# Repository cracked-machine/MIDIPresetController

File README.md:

# MIDIPresetController

This is a simple MIDI controller for Guitar FX pedals. An [STM32L011D4](HW/techdocs/stm32l011d4_datasheet.pdf) is used to detect stomp switch presses by the user and output MIDI signals via a DIN5 connector.

The project is designed to fit into a [Hammond 1455J1602](HW/techdocs/Hammond_1455J1602BK_enclosure.pdf) enclosure. 

3D models can be found here for the [end plate bezel](https://3dviewer.net#model=https://raw.githubusercontent.com/cracked-machine/MIDIPresetController/master/HW/res/3d/1455J1602/J%20Bezel%20Closed.igs) and [main extrusion](https://3dviewer.net#model=https://raw.githubusercontent.com/cracked-machine/MIDIPresetController/master/HW/res/3d/1455J1602/J%20Extrusion%20160mm.igs)

This is an extruded alu case. The PCB slides in from one side.  

The stomp switches are panel mounted on the front side of the enclosure with connecting wires to rear of the PCB (via molex KK254 connectors)

It is powered by a 3v3 CR2032 cell, held by a battery clip, which is mounted on the rear side of the PCB. Internal voltage reference of the MCU is used to measure remaining battery. An LED mounted on the front of the PCB and connected to GPIO indicates low battery power to the user.

The MIDI channel can be selected using the DIP switch on the rear side of the PCB.  The MIDI output connector (DIN5) is mounted to the end plate bezel of the enclosure

A 10-pin ARM SWD programming connector is mounted to the rear of the PCB. 

A removable "belly plate" on the enclosure provides access to the battery, MIDI DIP switch and SWD connector.  

### Development Environment

YOu can run this project from within a container and program the board via a Segger JLink. This uses `JLinkRemoteServer` to establish a connect between the container environment and the device connected to the `host` PC. To enable this connection, run the follow command on the __host__ terminal:

```
JLinkRemoteServer --select USB
```

See [stm32_dev_docker/README.md](https://github.com/cracked-machine/stm32_dev_docker) for instructions on using the `development environment` for this project.

Note: this project is currently configured for a specific version of CMake and ARM compiler. The paths are hard-coded in the project [here](.vscode/settings.json)

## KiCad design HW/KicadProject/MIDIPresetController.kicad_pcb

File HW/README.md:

# MIDIPresetController

This is the doc for the [hardware project files](KicadProject)

This project has the following dependencies to [KicadLibrary](HW/KicadLibrary):

- BATTERY/GenericCoinCellHolders/GenericCoinCellHolders

## Schematic 

1. System

2. Input 

3. MCU

4. Output

## Pinout 

## PCB

1. Front

2. Back

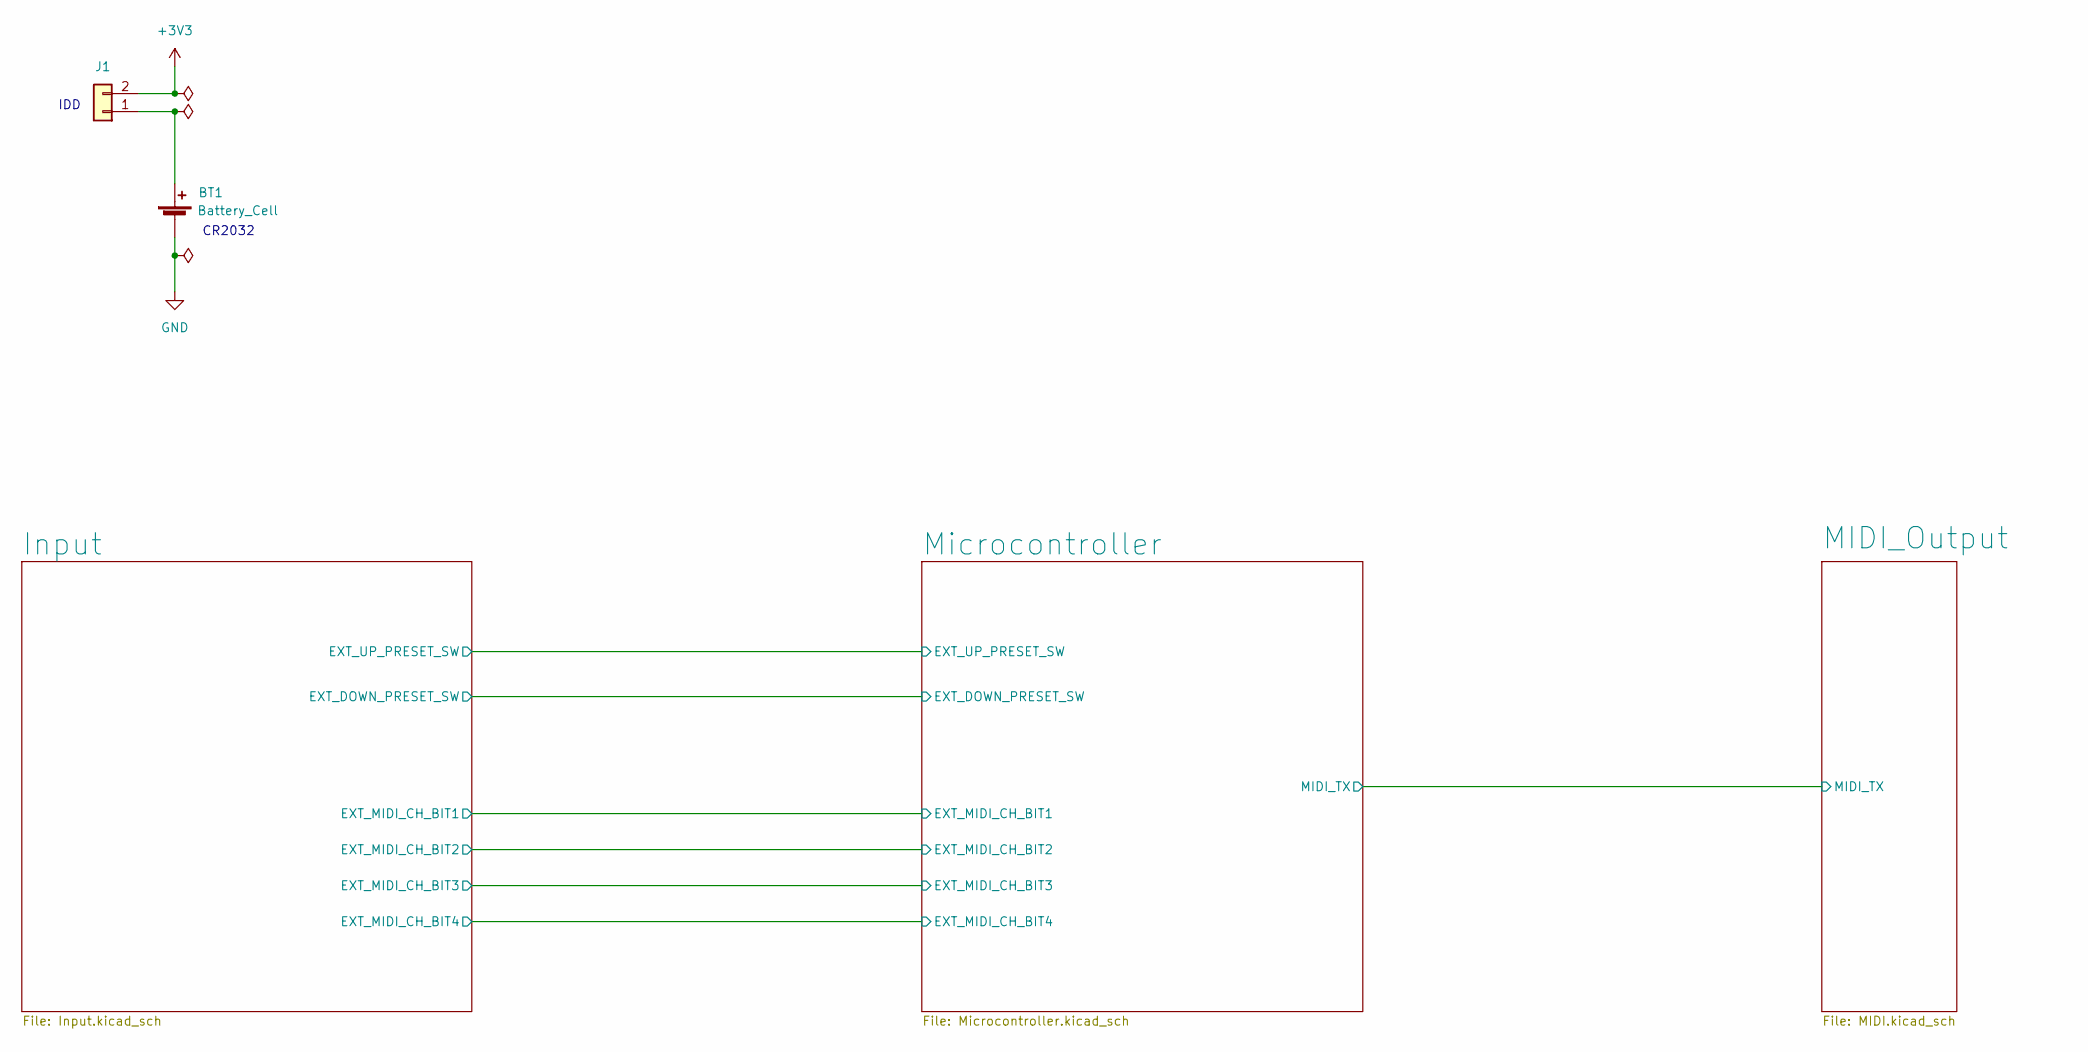
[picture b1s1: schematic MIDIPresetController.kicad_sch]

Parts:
BT1: Battery_Cell; CR2032
J1: Conn_01x02; PinHeader_1x02_P2.54mm_Vertical

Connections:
+3V3: J1.2; also elsewhere on the board
GND: BT1.2 (-); also elsewhere on the board
unnamed: BT1.1 (+), J1.1

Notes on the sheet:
CR2032
IDD

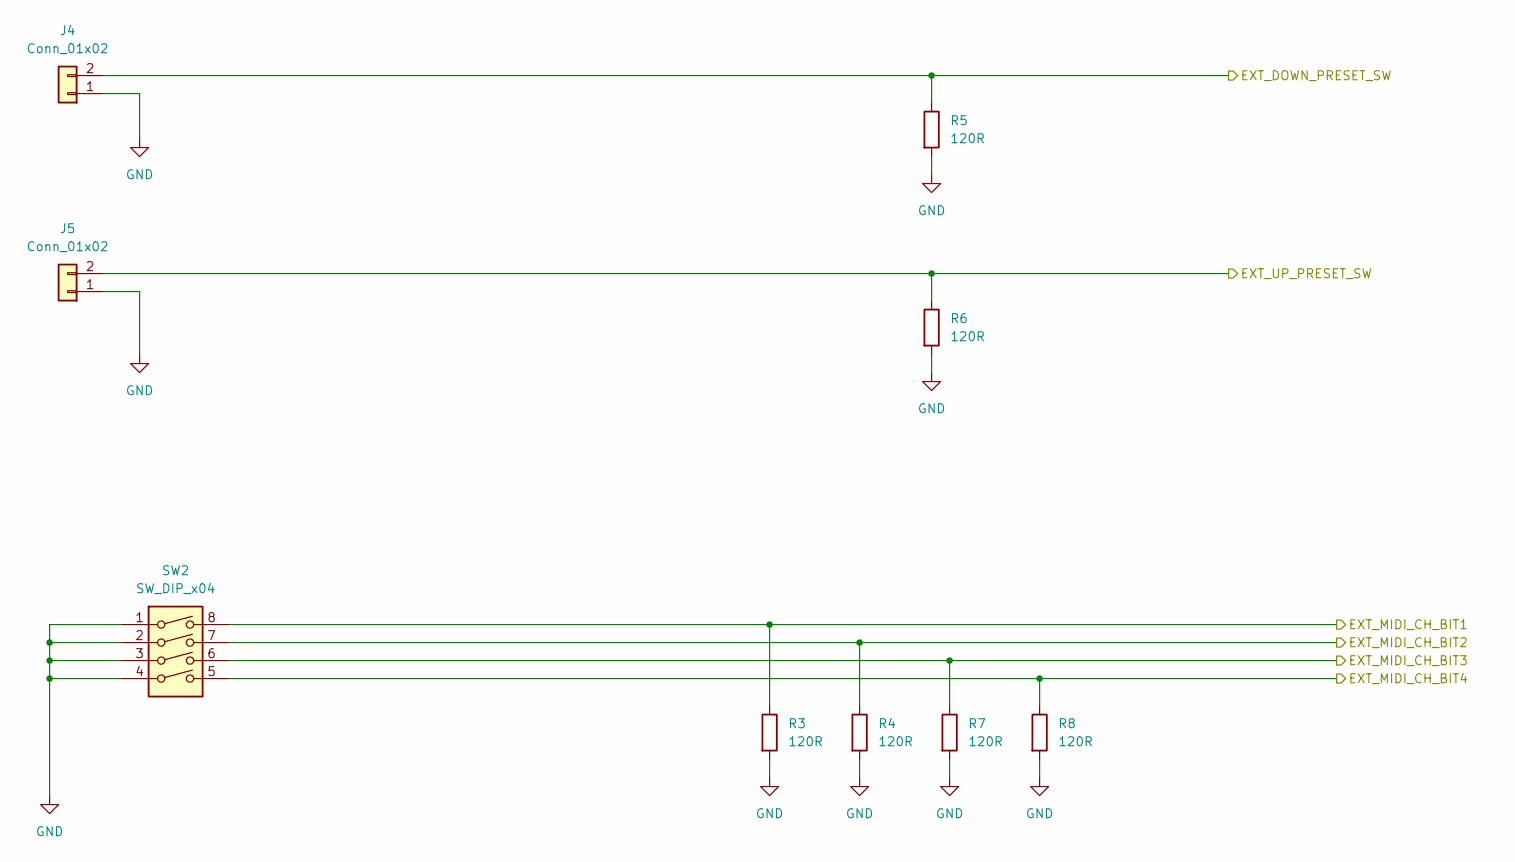
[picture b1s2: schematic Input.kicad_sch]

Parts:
J4, J5: Conn_01x02; PinHeader_1x02_P2.54mm_Horizontal
R3, R4, R5, R6, R7, R8: 120R; R_0805_2012Metric_Pad1.20x1.40mm_HandSolder
SW2: SW_DIP_x04; SW_DIP_SPSTx04_Slide_6.7x11.72mm_W7.62mm_P2.54mm_LowProfile

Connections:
/Microcontroller/EXT_DOWN_PRESET_SW: J4.2, R5.1; also elsewhere on the board
/Microcontroller/EXT_MIDI_CH_BIT1: R3.1, SW2.8; also elsewhere on the board
/Microcontroller/EXT_MIDI_CH_BIT2: R4.1, SW2.7; also elsewhere on the board
/Microcontroller/EXT_MIDI_CH_BIT3: R7.1, SW2.6; also elsewhere on the board
/Microcontroller/EXT_MIDI_CH_BIT4: R8.1, SW2.5; also elsewhere on the board
/Microcontroller/EXT_UP_PRESET_SW: J5.2, R6.1; also elsewhere on the board
GND: J4.1, J5.1, R3.2, R4.2, R5.2, R6.2, R7.2, R8.2, SW2.1, SW2.2, SW2.3, SW2.4; also elsewhere on the board

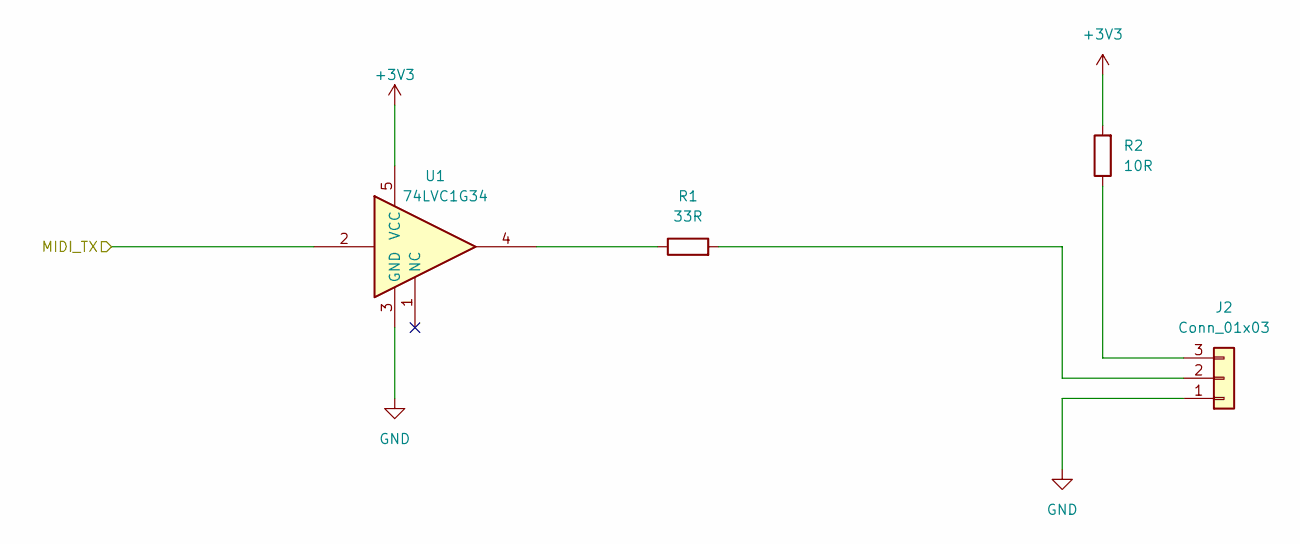
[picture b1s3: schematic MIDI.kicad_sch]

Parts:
J2: Conn_01x03; PinHeader_1x03_P2.54mm_Horizontal
R1: 33R; R_0805_2012Metric_Pad1.20x1.40mm_HandSolder
R2: 10R; R_0805_2012Metric_Pad1.20x1.40mm_HandSolder
U1: 74LVC1G34; SOT-23-5_HandSoldering

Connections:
+3V3: R2.2, U1.5 (VCC); also elsewhere on the board
/MIDI_Output/MIDI_TX: U1.2; also elsewhere on the board
GND: J2.1, U1.3 (GND); also elsewhere on the board
unnamed: J2.2, R1.2
unnamed: J2.3, R2.1
unnamed: R1.1, U1.4

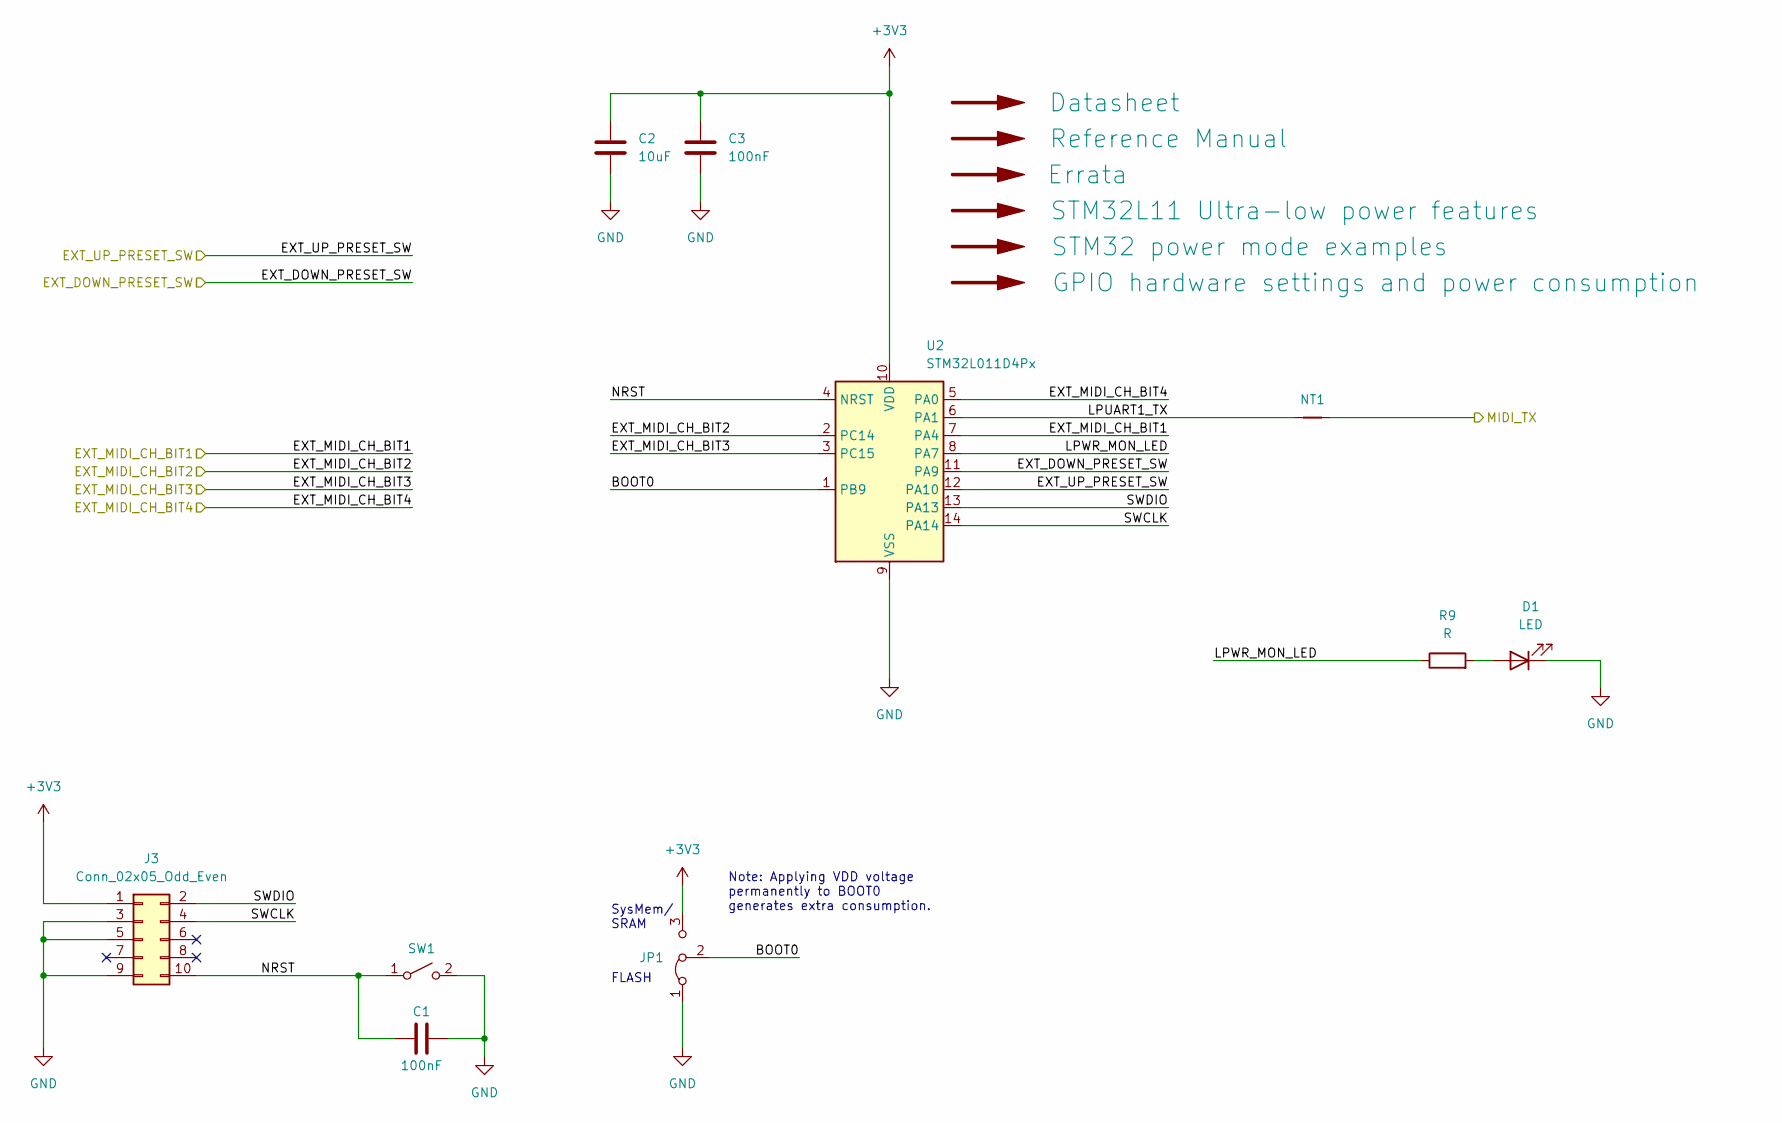
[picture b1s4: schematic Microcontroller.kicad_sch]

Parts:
C1, C3: 100nF; C_0805_2012Metric_Pad1.18x1.45mm_HandSolder
C2: 10uF; C_0805_2012Metric_Pad1.18x1.45mm_HandSolder
D1: LED; LED_D5.0mm
J3: Conn_02x05_Odd_Even; PinHeader_2x05_P1.27mm_Vertical_SMD
JP1: Jumper_3_Bridged12; PinHeader_1x03_P2.54mm_Vertical
NT1: NetTie_2; NetTie-2_SMD_Pad0.5mm
R9: R; R_0805_2012Metric_Pad1.20x1.40mm_HandSolder
SW1: SW_SPST; SW_PUSH_6mm
U2: STM32L011D4Px; TSSOP-14_4.4x5mm_P0.65mm

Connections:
+3V3: C2.1, C3.1, J3.1, JP1.3 (B), U2.10 (VDD); also elsewhere on the board
/MIDI_Output/MIDI_TX: NT1.2; also elsewhere on the board
/Microcontroller/BOOT0: JP1.2 (C), U2.1 (PB9)
/Microcontroller/EXT_DOWN_PRESET_SW: U2.11 (PA9); also elsewhere on the board
/Microcontroller/EXT_MIDI_CH_BIT1: U2.7 (PA4); also elsewhere on the board
/Microcontroller/EXT_MIDI_CH_BIT2: U2.2 (PC14); also elsewhere on the board
/Microcontroller/EXT_MIDI_CH_BIT3: U2.3 (PC15); also elsewhere on the board
/Microcontroller/EXT_MIDI_CH_BIT4: U2.5 (PA0); also elsewhere on the board
/Microcontroller/EXT_UP_PRESET_SW: U2.12 (PA10); also elsewhere on the board
/Microcontroller/LPUART1_TX: NT1.1, U2.6 (PA1)
/Microcontroller/LPWR_MON_LED: R9.1, U2.8 (PA7)
/Microcontroller/NRST: C1.1, J3.10, SW1.1 (A), U2.4 (NRST)
/Microcontroller/SWCLK: J3.4, U2.14 (PA14)
/Microcontroller/SWDIO: J3.2, U2.13 (PA13)
GND: C1.2, C2.2, C3.2, D1.1 (K), J3.3, J3.5, J3.9, JP1.1 (A), SW1.2 (B), U2.9 (VSS); also elsewhere on the board
unnamed: D1.2 (A), R9.2

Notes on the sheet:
SysMem/ SRAM
FLASH
Note: Applying VDD voltage permanently to BOOT0 generates extra consumption.

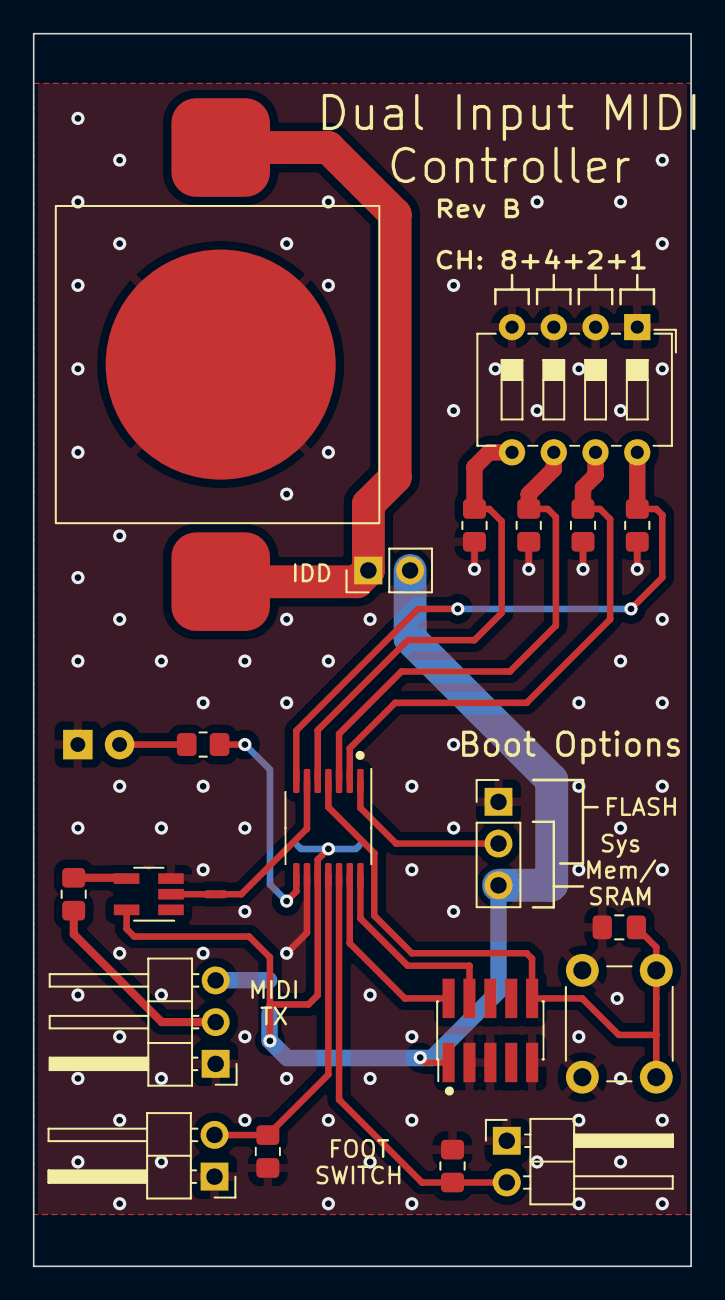
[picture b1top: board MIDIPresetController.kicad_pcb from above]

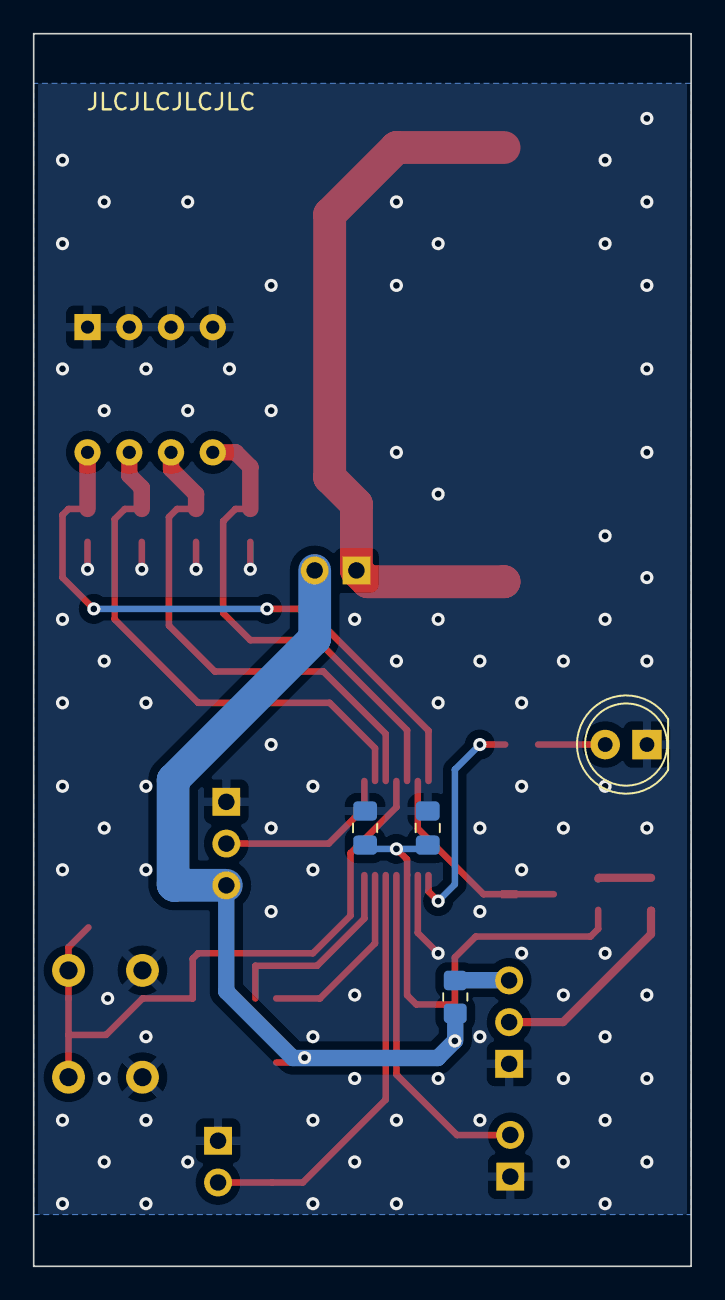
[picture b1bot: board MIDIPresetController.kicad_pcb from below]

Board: 2 copper layers, 40.0 x 75.0 mm, 25 parts (4 on the bottom side), 20 nets.

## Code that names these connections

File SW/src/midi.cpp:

#include <midi.hpp>
#include <array>
#include <stdint.h>
#include <stm32l011xx.h>
#if DEBUG
    #include <SEGGER_RTT.h>
#endif
#include <led.hpp>

const volatile uint32_t DIPSW_DEBOUNCE_COOLDOWN{ 200 };
volatile uint32_t dipsw_pa0_prev_cnt = 0;
volatile uint32_t dipsw_pa4_prev_cnt = 0;
volatile uint32_t dipsw_pc14_prev_cnt = 0;
volatile uint32_t dipsw_pc15_prev_cnt = 0;
const volatile uint32_t FOOTSW_DEBOUNCE_COOLDOWN{ 100 };
volatile uint32_t footsw_up_prev_cnt = 0;
volatile uint32_t footsw_down_prev_cnt = 0;

// MIDI CC messages - 0xnc, 0xcc, 0xvv 
// LSB first: starting left to right
//   n is the status type (0xB)
//   c is the MIDI channel
//   cc is the controller number (0-127)
//   vv is the controller value (0-127)
// 0x82 is nemesis preset up cmd 
std::array<uint8_t, 3> midi_up_preset_msg{0xB0, 0x82, 0x00};  

// MIDI CC messages - 0xnc, 0xcc, 0xvv 
// LSB first: starting left to right
//   n is the status type (0xB)
//   c is the MIDI channel
//   cc is the controller number (0-127)
//   vv is the controller value (0-127)
// 0x80 is nemesis preset down cmd
std::array<uint8_t, 3> midi_down_preset_msg{0xB0, 0x80, 0x00}; 

uint8_t midi_channel{0};    // only 4 lsb bits used 
#define midi_chan_mask (midi_channel << 0U)
uint8_t midi_preset_counter{8};

// bytes will only be processed by LPUART ISR when counts are zero, so start at non-zero
uint16_t msg_tx_count{0};


enum preset_enum {
    UP_COMMAND,
    DOWN_COMMAND,
    IDLE
};

preset_enum transmit_command_direction = IDLE;

void increment_midi_preset()
{
    if (midi_preset_counter > 0)
    {
        midi_preset_counter--;
        midi_down_preset_msg[2] = midi_preset_counter;
        #if DEBUG
            SEGGER_RTT_printf(0, "DOWN %d\r\n", midi_preset_counter); 
        #endif
        print_midi_msg();
    }    
    transmit_command_direction = DOWN_COMMAND;
}

void decrement_midi_preset()
{
    if (midi_preset_counter < 0xFE)
    {
        midi_preset_counter++;
        midi_up_preset_msg[2] = midi_preset_counter;
        #if DEBUG
            SEGGER_RTT_printf(0, "UP %d\r\n", midi_preset_counter); 
        #endif
        print_midi_msg();
    }
    transmit_command_direction = UP_COMMAND;    
}

void send_midi_bytes()
{
    if (transmit_command_direction == UP_COMMAND)
    {
        // transmit up preset bytes until count = 0
        if (msg_tx_count == 0)
        {
            LPUART1->ICR |= USART_ICR_TCCF_Msk;
        }
        if (msg_tx_count == midi_down_preset_msg.size())
        {
            msg_tx_count = 0;
            LPUART1->CR1 &=  ~( USART_CR1_TXEIE_Msk );                           
        }
        else
        {
            // transfer next byte     
            LPUART1->TDR = (midi_down_preset_msg[msg_tx_count] & 0xFF);       
            msg_tx_count++;
        }
    }

    if (transmit_command_direction == DOWN_COMMAND)
    {
        if (msg_tx_count == 0)
        {
            LPUART1->ICR |= USART_ICR_TCCF_Msk;
        }
        if (msg_tx_count == midi_down_preset_msg.size())
        {
            msg_tx_count = 0;
            LPUART1->CR1 &=  ~( USART_CR1_TXEIE_Msk );                           
        }
        else
        {
            // transfer next byte     
            LPUART1->TDR = (midi_down_preset_msg[msg_tx_count] & 0xFF);       
            msg_tx_count++;
        }
    }    
}

void print_midi_msg()
{
    #if DEBUG
        SEGGER_RTT_printf(0, "midi_down_preset_msg:");
        SEGGER_RTT_printf(0, "0x%x", midi_down_preset_msg[2]);
        SEGGER_RTT_printf(0, "%x", midi_down_preset_msg[1]);
        SEGGER_RTT_printf(0, "%x\r\n", midi_down_preset_msg[0]); 
        SEGGER_RTT_printf(0, "midi_up_preset_msg:");
        SEGGER_RTT_printf(0, "0x%x", midi_up_preset_msg[2]);
        SEGGER_RTT_printf(0, "%x", midi_up_preset_msg[1]);
        SEGGER_RTT_printf(0, "%x\r\n", midi_up_preset_msg[0]);    
    #endif
}

/// @brief Write the 4 LSB according to the dip switch settings
void read_midi_channel()
{
    // PA4  - EXT_MIDI_CH_BIT1
    if (GPIOA->IDR & (GPIO_IDR_ID4_Msk))
    {
        midi_channel |= (1U << 0U);
    }
    // PC14 - EXT_MIDI_CH_BIT2
    if (GPIOC->IDR & (GPIO_IDR_ID14_Msk))
    {
        midi_channel |= (1U << 1U);
    }
    // PC15 - EXT_MIDI_CH_BIT3
    if (GPIOC->IDR & (GPIO_IDR_ID15_Msk))
    {
        midi_channel |= (1U << 2U);
    }    
    // PA0  - EXT_MIDI_CH_BIT4
    if (GPIOA->IDR & (GPIO_IDR_ID0_Msk))
    {
        midi_channel |= (1U << 3U);
    }    

    // most sig. nibble of `midi_channel` should be 0000, so we can shift the 
    // whole byte in without clobbering the existing MSB status bit.
    midi_up_preset_msg[0] |= midi_channel << 0U;
    midi_down_preset_msg[0] |= midi_channel << 0U;
}

////////////////////////////////
/// Interupt Service Routines
////////////////////////////////

extern "C" {
void EXTI4_15_IRQHandler()
{
    // #if DEBUG
    // SEGGER_RTT_printf(0, "EXTI4_15_IRQHandler\r\n");
    // #endif

    // PA9 EXTI - EXT_DOWN_PRESET_SW
    if (EXTI->PR & EXTI_IMR_IM9_Msk)                
    {
        uint32_t tmp_cnt = TIM21->CNT;
        if ((tmp_cnt - footsw_down_prev_cnt) > FOOTSW_DEBOUNCE_COOLDOWN)
        {
            toggle_led();   // visual debug. This should be removed at some point
            increment_midi_preset();
            
            // Enable TXE (tx data reg transferred) interrupts to start the LPUART transmission
            LPUART1->CR1 |=  ( USART_CR1_TXEIE_Msk );   
        }
        else
        {
            // #if DEBUG
            // SEGGER_RTT_printf(0, "Debounced\r\n");
            // #endif
        }
        EXTI->PR |= (EXTI_PR_PIF9_Msk);
        footsw_down_prev_cnt = tmp_cnt;
    }

    // PA10 EXTI - EXT_UP_PRESET_SW
    else if (EXTI->PR & EXTI_IMR_IM10_Msk)         
    {
        uint32_t tmp_cnt = TIM21->CNT;
        if ((tmp_cnt - footsw_up_prev_cnt) > FOOTSW_DEBOUNCE_COOLDOWN)
        {
            toggle_led();   // visual debug. This should be removed at some point
            decrement_midi_preset();
            // Enable TXE (tx data reg transferred) interrupts to start the LPUART transmission
            LPUART1->CR1 |=  ( USART_CR1_TXEIE_Msk );   
        }
        else
        {
            // #if DEBUG
            // SEGGER_RTT_printf(0, "Debounced\r\n");
            // #endif
        }
        EXTI->PR |= (EXTI_PR_PIF10_Msk);            
        footsw_up_prev_cnt = tmp_cnt;
    }
}

void LPUART1_IRQHandler()
{
    
    // if last byte was transferred from TDR to shift register then we are ready to send next byte
    if ((LPUART1->ISR & USART_ISR_TXE) != 0U)
    {
        send_midi_bytes();
    }
}

}

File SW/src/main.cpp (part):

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    
    // LED //
    /////////
    GPIOA->MODER |= (GPIO_MODER_MODE7_0);                               // config PA7 as output (0x01)
    GPIOA->MODER &= ~(GPIO_MODER_MODE7_1);
    GPIOA->OTYPER &= ~(GPIO_OTYPER_OT_7);                               // setup p7 as pushpull, highspeed, no PU/PD
    GPIOA->OSPEEDR |= (GPIO_OSPEEDER_OSPEED7_Msk);
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    SYSCFG->EXTICR[2] |= (SYSCFG_EXTICR3_EXTI9_PA);                     // map Port A GPIOs to EXTI9
    SYSCFG->EXTICR[2] |= (SYSCFG_EXTICR3_EXTI10_PA);                    // map Port A GPIOs to EXTI10
                                                                        
    // PA10
    GPIOA->MODER &= ~((GPIO_MODER_MODE10_0) | (GPIO_MODER_MODE10_1));   // setup pa10 gpio as input (0x00)
    GPIOA->PUPDR |= (GPIO_PUPDR_PUPD10_0);                              // set pa10 gpio pullup (0x01)
    GPIOA->PUPDR &= ~(GPIO_PUPDR_PUPD10_1);
    EXTI->IMR |= EXTI_IMR_IM10_Msk;                                     // enable interupt request in interrupt mask register
    EXTI->FTSR |= EXTI_FTSR_FT10_Msk;                                   // program trigger resistors with edge detection

    // PA9 
    GPIOA->MODER &= ~((GPIO_MODER_MODE9_0) | (GPIO_MODER_MODE9_1));     // setup pa10 gpio as input (0x00)
    GPIOA->PUPDR |= (GPIO_PUPDR_PUPD9_0);                               // set pa10 gpio pullup (0x01)
    GPIOA->PUPDR &= ~(GPIO_PUPDR_PUPD9_1);
    EXTI->IMR |= EXTI_IMR_IM9_Msk;                                      // enable interupt request in interrupt mask register
    EXTI->FTSR |= EXTI_FTSR_FT9_Msk;                                    // program trigger resistors with edge detection

    // PA4 - EXT_MIDI_CH_BIT1
    GPIOA->MODER &= ~((GPIO_MODER_MODE4_0) | (GPIO_MODER_MODE4_1));     // setup PA4 gpio as input (0x00)
    GPIOA->PUPDR |= (GPIO_PUPDR_PUPD4_0);                               // set pa4 gpio pullup (0x01)
    GPIOA->PUPDR &= ~(GPIO_PUPDR_PUPD4_1);
    
    // PC14 - EXT_MIDI_CH_BIT2
    GPIOC->MODER &= ~((GPIO_MODER_MODE14_0) | (GPIO_MODER_MODE14_1));   // setup PC14 gpio as input (0x00)
    GPIOC->PUPDR |= (GPIO_PUPDR_PUPD14_0);                              // set pc14 gpio pullup (0x01)
    GPIOC->PUPDR &= ~(GPIO_PUPDR_PUPD14_1);

    // PC15 - EXT_MIDI_CH_BIT3
    GPIOC->MODER &= ~((GPIO_MODER_MODE15_0) | (GPIO_MODER_MODE15_1));   // setup PC15 gpio as input (0x00)
    GPIOC->PUPDR |= (GPIO_PUPDR_PUPD15_0);                              // set pc15 gpio pullup (0x01)
    GPIOC->PUPDR &= ~(GPIO_PUPDR_PUPD15_1);
    
    // PA0 - EXT_MIDI_CH_BIT4
    GPIOA->MODER &= ~((GPIO_MODER_MODE0_0) | (GPIO_MODER_MODE0_1));     // setup PA0 gpio as input (0x00)
    GPIOA->PUPDR |= (GPIO_PUPDR_PUPD0_0);                               // set pa0 gpio pullup (0x01)
    GPIOA->PUPDR &= ~(GPIO_PUPDR_PUPD0_1);
    
    NVIC_EnableIRQ(EXTI4_15_IRQn);                                      // configure nvic irq channel and prio
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
    // LPUART //
    ////////////
    GPIOA->MODER |= (GPIO_MODER_MODE1_1);                               // Set PA1 as alt func (0x10) 
    GPIOA->MODER &= ~(GPIO_MODER_MODE1_0);
    volatile uint32_t GPIOA_AF_LPUART = 0x6;
    GPIOA->AFR[0] |= (GPIOA_AF_LPUART << GPIO_AFRL_AFSEL1_Pos);         // Set alt func on pin pa1 to lpuart1
    GPIOA->OSPEEDR |= GPIO_OSPEEDER_OSPEED1_Msk;                        // "very fast" speed
    
    RCC->APB1ENR |= RCC_APB1ENR_LPUART1EN_Msk;                          // enable the APB1 bus clock used by LPUART
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
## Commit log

2022-12-06 Runs main loop on target with JLink debug
2022-12-11 added docker submodule, enabled TCP debug to target using JLinkRemoteServer
2022-12-11 updated readme in submodule
2022-12-12 tidied loose files into src/inc dirs
2022-12-12 Added blinky
2023-01-03 added setting to workspace settings.json
2023-01-03 Added image options
2023-01-03 added comment
2023-01-03 updated Jlink path
2023-01-03 used builtin size and objcopy
2023-01-03 updated submodule
2023-01-06 Add KicadLibrary submodule
2023-01-06 Added kiad project in HW dir
2023-01-06 added license, updated gitignore and readme
2023-01-06 moved files from top level to SW dir. SVD moved to HW dir
2023-01-06 testing embedded 3d view
2023-01-06 replaced 3d viewer with link
2023-01-06 updated readme links
2023-04-09 updated submodules
2023-04-09 updated syntax
2023-04-09 updated path and removed port
2023-04-09 removed autosave files
2023-04-09 Updated to kicad 7.0.1, added stm32 doc links into schema page, regen pdf schema
2023-04-09 added kicad backup files
2023-04-09 refactored led code
2023-04-09 moved system isr to separate c file
2023-04-09 add EXTI9/10
2023-04-09 Added TODO
2023-04-09 enabled timer
2023-04-10 disabled linker warning
2023-04-10 tidied up comments
2023-04-10 enabled HSI+PLL to 32MHz sysclk
2023-04-10 add midi spec 1.0 to SW
2023-04-10 added PLL defs
2023-04-14 enabled LPUART1
2023-04-14 added exti timer debounce
2023-04-14 exti triggers single uart msg
2023-04-16 added Segger RTT
2023-04-16 enabled dip sw exti
2023-04-17 added midi commands
2023-04-17 added nemsis midi impl chart
2023-04-30 moved techdocs
2023-04-30 added extensions
2023-04-30 updated clock timings
2023-04-30 seperated led/tim function
2023-04-30 renamed isr
2023-04-30 added rcc
2023-04-30 separated files out, added config generator based selection for rtt
2023-04-30 replaced variables with target_compile_options
